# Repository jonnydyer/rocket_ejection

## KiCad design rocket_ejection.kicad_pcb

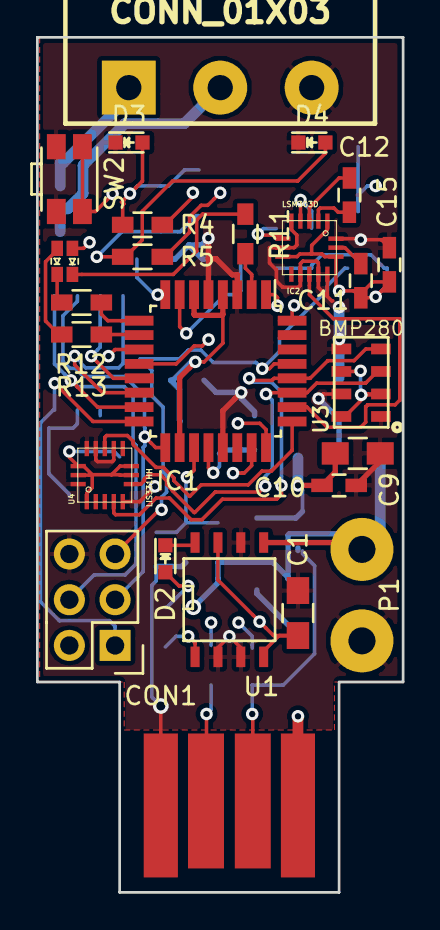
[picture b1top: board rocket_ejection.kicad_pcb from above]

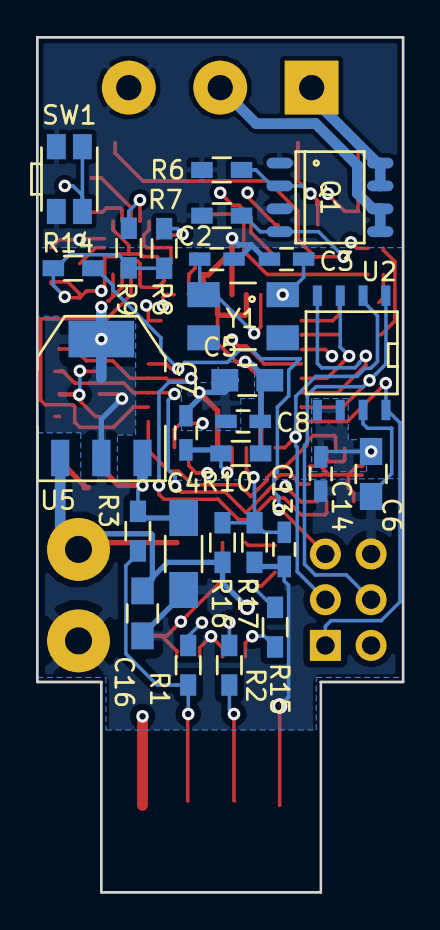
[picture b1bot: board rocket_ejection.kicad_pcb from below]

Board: 4 copper layers, 20.3 x 47.5 mm, 52 parts (27 on the bottom side), 41 nets.

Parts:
C1, C5, C6, C9, C16: 10u; C_0805_HandSoldering
C2, C3: 22p; C_0603_HandSoldering
C4: 3.3u; C_1206_HandSoldering
C7: 10n; C_0603_HandSoldering
C8, C10, C13, C14, C15: 100n; C_0603_HandSoldering
C11: 4.7u; C_0603_HandSoldering
C12: 0.22u; C_0603_HandSoldering
CON1: AVR-ISP-6; Pin_Header_Straight_2x03
D1: Led_RGBA; LED_RGB_DUAL_0606
D2, D3, D4: Led_Small; LED-0603
IC1: ATMEGA328P-A; TQFP-32_7x7mm_Pitch0.8mm
IC2: LSM303D; LGA-16-3x3
P1: Battery; SolderWirePad_2x_1-5mmDrill
P2: USB_A; usb-PCB
P3: CONN_01X03; mstba_2,5%2f3-g-5,08
Q1: FDS6890A; SO-8
R1, R2, R11: 68R; R_0603_HandSoldering
R3: 1k5; R_0603_HandSoldering
R4, R5: 100R; R_0603_HandSoldering
R6, R7, R14: 10k; R_0603_HandSoldering
R8, R9, R10: 2k2; R_0603_HandSoldering
R12, R13: 10R; R_0603_HandSoldering
R15: 470R; R_0603_HandSoldering
R16: 300k; R_0603_HandSoldering
R17: 100k; R_0603_HandSoldering
SW1, SW2: SW_PUSH; SW_SPST_EVQP7A
U1: MAX1811; SOIC-8-N
U2: Dataflash; SOIC-8-N
U3: BMP280; LGA8
U4: LIS331HH; LGA-16-3x3
U5: LT1129CST-3.3; SOT-223
Y1: 16MHz; Crystal_SMD_0603_4Pads

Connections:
+BATT: C16.1, P1.1, R16.1, U1.5, U5.1
/MISO: CON1.1, IC1.16, U2.8
/MOSI: CON1.4, IC1.15, U2.1
/PC2: IC1.25, U4.11
/PC3: IC1.26, IC2.11
/PYROA: D3.2, Q1.2, R4.2, R6.2
/PYROB: D4.2, Q1.4, R5.2, R7.2
/SCK: CON1.3, IC1.17, U2.2
/SCL: IC1.28, IC2.4, R9.1, U3.4, U4.4
/SDA: IC1.27, IC2.6, R8.1, U3.3, U4.6
/~CS: IC1.14, U2.4
/~DF_RST: IC1.13, U2.3
/~RESET: CON1.5, IC1.29, R14.1
GNDREF: C1.2, C2.1, C3.1, C4.2, C5.2, C6.2, C7.1, C8.2, C9.2, C10.2, C13.2, C14.2, C15.2, C16.2, CON1.6, D3.1, D4.1, IC1.3, IC1.5, IC1.21, IC2.5, IC2.7, IC2.10, IC2.12, IC2.13, IC2.16, P1.2, P2.4, P3.3, Q1.1, Q1.3, R6.1, R7.1, R17.2, SW1.2, SW2.2, U1.2, U1.3, U1.6, U2.7, U3.1, U3.5, U3.7, U4.5, U4.10, U4.12, U4.13, U4.16, U5.2, U5.4
unnamed: C1.1, P2.1, R15.2, U1.1, U1.4, U1.7
unnamed: C2.2, IC1.7, Y1.2
unnamed: C3.2, IC1.8, Y1.1
unnamed: C7.2, IC1.20, R10.2
unnamed: C11.1, IC2.15
unnamed: C12.1, IC2.3
unnamed: C12.2, IC2.2
unnamed: C13.1, IC1.19, R16.2, R17.1
unnamed: D1.1, R11.1
unnamed: D1.2, R12.1
unnamed: D1.3, R13.1
unnamed: D2.1, U1.8
unnamed: D2.2, R15.1
unnamed: IC1.1, R2.2
unnamed: IC1.2, R11.2
unnamed: IC1.9, R12.2
unnamed: IC1.10, R13.2
unnamed: IC1.11, SW2.1
unnamed: IC1.12, SW1.1
unnamed: IC1.23, R4.1
unnamed: IC1.24, R5.1
unnamed: IC1.32, R1.2
unnamed: P2.2, R1.1, R3.1
unnamed: P2.3, R2.1
unnamed: P3.1, Q1.7, Q1.8
unnamed: P3.2, Q1.5, Q1.6
VCC: C4.1, C5.1, C6.1, C8.1, C9.1, C10.1, C11.2, C14.1, C15.1, CON1.2, D1.4, IC1.4, IC1.6, IC1.18, IC2.1, IC2.8, IC2.14, R3.2, R8.2, R9.2, R10.1, R14.2, U2.5, U2.6, U3.2, U3.6, U3.8, U4.1, U4.7, U4.8, U4.14, U4.15, U5.3

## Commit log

2019-06-29 Divided kicad repo into individual projects
